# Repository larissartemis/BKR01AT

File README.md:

# BKR01AT
Reavaliação de Circuitos Impressos - BKR01AT - IC / UFAL

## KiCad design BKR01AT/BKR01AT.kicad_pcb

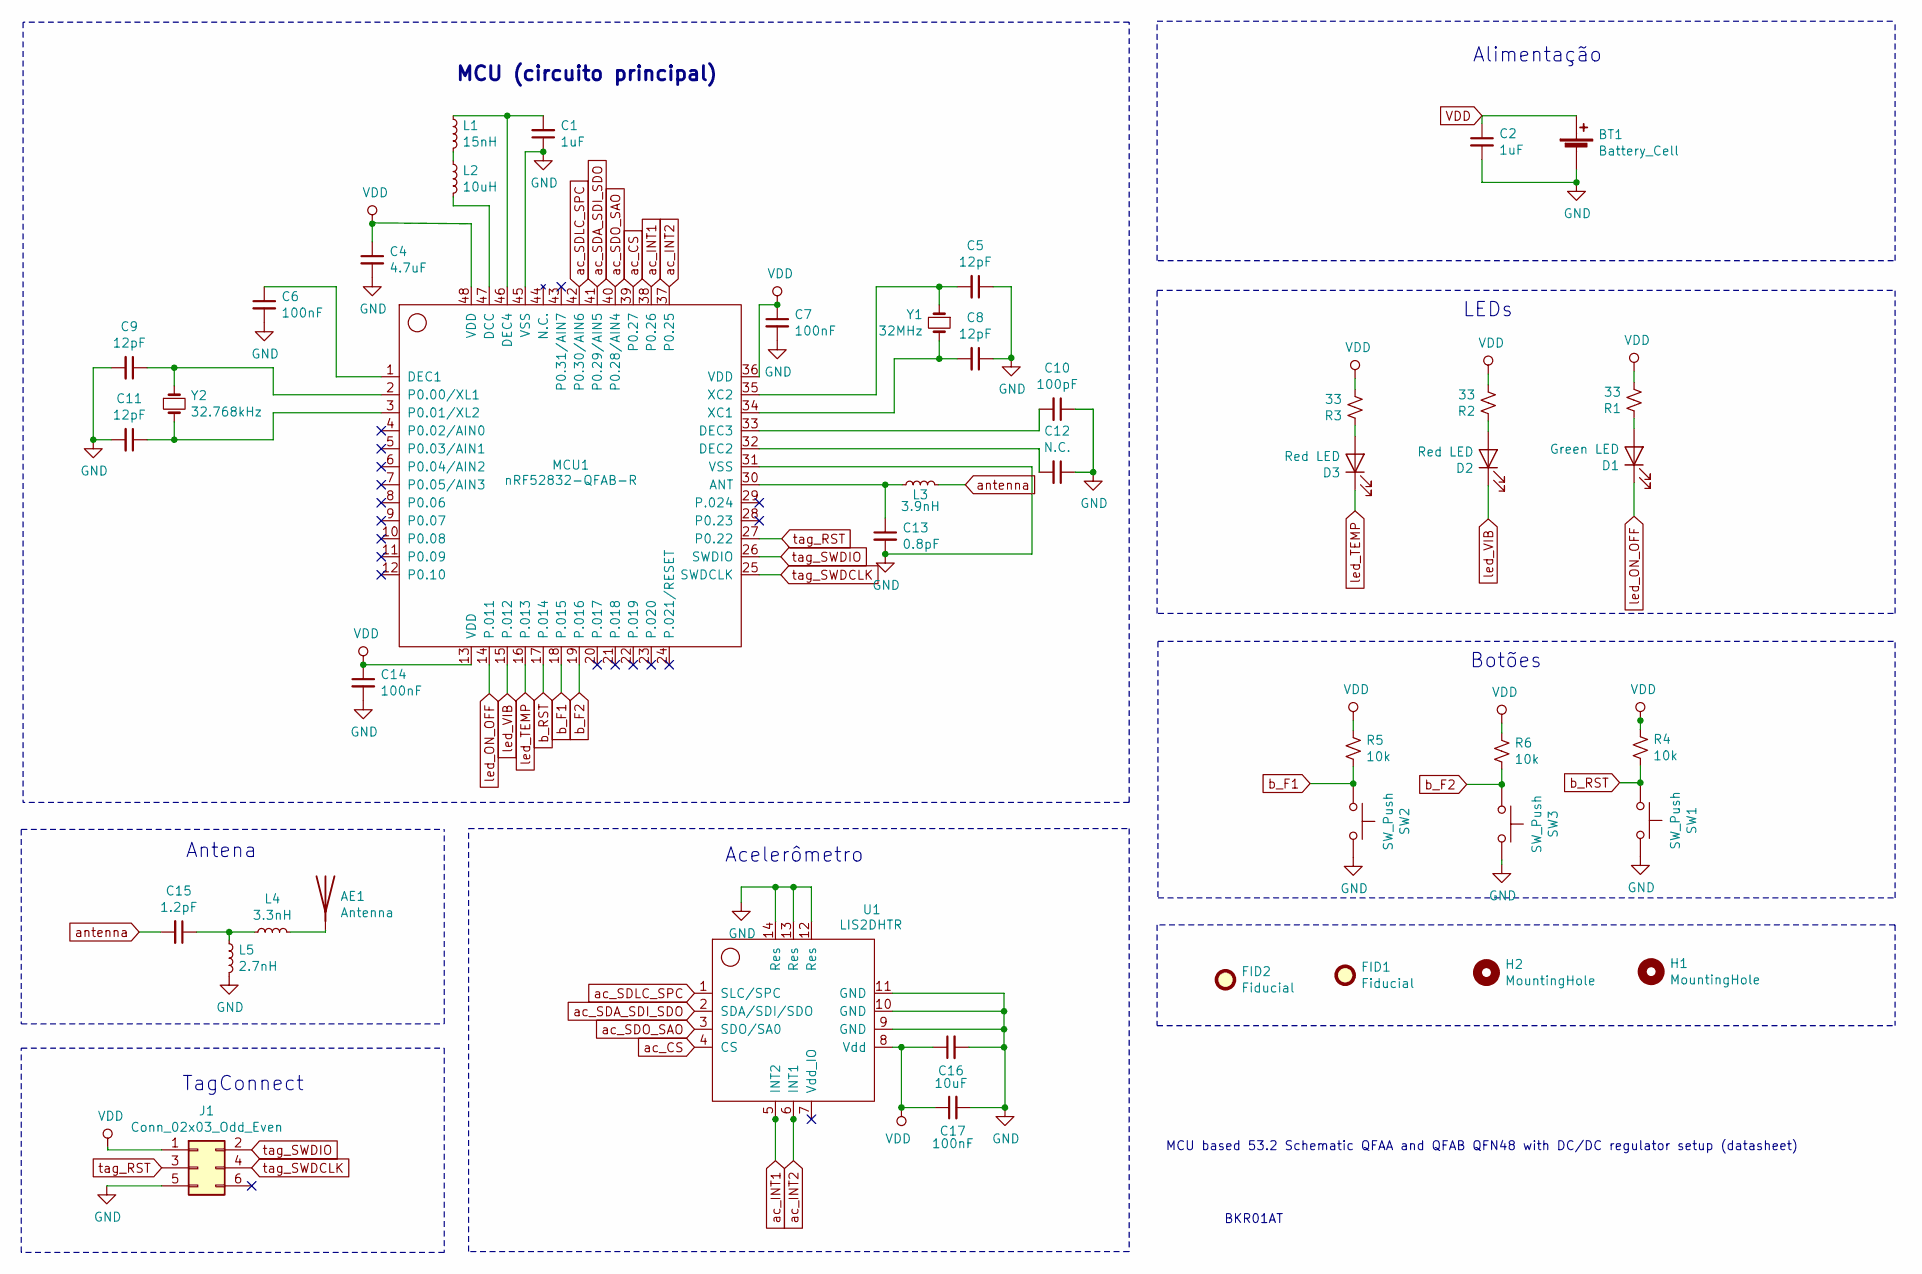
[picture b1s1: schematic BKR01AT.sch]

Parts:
AE1: Antenna; ANT_2450AT18B100E; Part Number 2450AT18B100E
BT1: Battery_Cell; BatteryHolder_MPD_BC2003_1x2032; Part Number CR2032R-HE1
C1, C2: 1uF; C_0402_1005Metric
C4: 4.7uF; C_0402_1005Metric
C5, C8, C9, C11: 12pF; C_0402_1005Metric
C6, C7, C14, C17: 100nF; C_0402_1005Metric
C10: 100pF; C_0402_1005Metric
C12: N.C.; C_0402_1005Metric
C13: 0.8pF; C_0402_1005Metric
C15: 1.2pF; C_0402_1005Metric
C16: 10uF; C_0402_1005Metric
D1: Green LED; LED_0603_1608Metric; Part Number 150060VS75000
D2: Red LED; LED_0603_1608Metric; Part Number 150060VS75000
D3: Red LED; LED_0603_1608Metric; Part Number 150060RS75000
FID1, FID2: Fiducial; Fiducial_0.5mm_Mask1mm
H1, H2: MountingHole; MountingHole_3.2mm_M3
J1: Conn_02x03_Odd_Even; Tag-Connect_TC2030-IDC-NL_2x03_P1.27mm_Vertical
L1: 15nH; L_0402_1005Metric
L2: 10uH; L_0402_1005Metric
L3: 3.9nH; L_0402_1005Metric
L4: 3.3nH; L_0402_1005Metric
L5: 2.7nH; L_0402_1005Metric
MCU1: nRF52832-QFAB-R; QFN-48-1EP_6x6mm_P0.4mm_EP4.6x4.6mm; Part Number nRF52832-QFAB-R
R1, R2, R3: 33; R_0402_1005Metric
R4, R5, R6: 10k; R_0402_1005Metric
SW1, SW2, SW3: SW_Push; SW_PUSH_6mm_H4.3mm; Part Number PTS636 SL43 LFS
U1: LIS2DHTR; LGA-14_2x2mm_P0.35mm_LayoutBorder3x4y; Part Number LIS2DHTR
Y1: 32MHz; Crystal_SMD_2016-4Pin_2.0x1.6mm
Y2: 32.768kHz; Crystal_SMD_3215-2Pin_3.2x1.5mm

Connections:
GND: BT1.2 (-), C1.1, C2.2, C4.2, C5.1, C6.2, C7.2, C8.1, C9.2, C10.1, C11.2, C12.1, C13.2, C14.2, C16.2, C17.2, J1.5, L5.2, MCU1.31 (VSS), MCU1.45 (VSS), SW1.2, SW2.2, SW3.2, U1.9 (GND), U1.10 (GND), U1.11 (GND), U1.12 (Res), U1.13 (Res), U1.14 (Res)
unnamed: AE1.1, L4.2
unnamed: C1.2, L1.1, MCU1.46 (DEC4)
unnamed: C5.2, MCU1.35 (XC2), Y1.1
unnamed: C6.1, MCU1.1 (DEC1)
unnamed: C8.2, MCU1.34 (XC1), Y1.2
unnamed: C9.1, MCU1.2 (P0.00/XL1), Y2.1
unnamed: C10.2, MCU1.33 (DEC3)
unnamed: C11.1, MCU1.3 (P0.01/XL2), Y2.2
unnamed: C12.2, MCU1.32 (DEC2)
unnamed: C13.1, L3.1, MCU1.30 (ANT)
unnamed: C15.1, L4.1, L5.1
unnamed: D1.2 (A), R1.1
unnamed: D2.2 (A), R2.1
unnamed: D3.2 (A), R3.1
unnamed: L1.2, L2.1
unnamed: L2.2, MCU1.47 (DCC)
VDD: BT1.1 (+), C2.1, C4.1, C7.1, C14.1, C16.1, C17.1, J1.1, MCU1.13 (VDD), MCU1.36 (VDD), MCU1.48 (VDD), R1.2, R2.2, R3.2, R4.1, R5.1, R6.1, U1.8 (Vdd)
ac_CS: MCU1.39 (P0.27), U1.4 (CS)
ac_INT1: MCU1.38 (P0.26), U1.5 (INT2)
ac_INT2: MCU1.37 (P0.25), U1.6 (INT1)
ac_SDA_SDI_SDO: MCU1.41 (P0.29/AIN5), U1.2 (SDA/SDI/SDO)
ac_SDLC_SPC: MCU1.42 (P0.30/AIN6), U1.1 (SLC/SPC)
ac_SDO_SAO: MCU1.40 (P0.28/AIN4), U1.3 (SDO/SA0)
antenna: C15.2, L3.2
b_F1: MCU1.18 (P.015), R5.2, SW2.1
b_F2: MCU1.19 (P.016), R6.2, SW3.1
b_RST: MCU1.17 (P.014), R4.2, SW1.1
led_ON_OFF: D1.1 (K), MCU1.14 (P.011)
led_TEMP: D3.1 (K), MCU1.16 (P.013)
led_VIB: D2.1 (K), MCU1.15 (P.012)
tag_RST: J1.3, MCU1.27 (P0.22)
tag_SWDCLK: J1.4, MCU1.25 (SWDCLK)
tag_SWDIO: J1.2, MCU1.26 (SWDIO)

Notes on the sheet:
MCU based 53.2 Schematic QFAA and QFAB QFN48 with DC/DC regulator setup (datasheet)
BKR01AT
TagConnect
Acelerômetro
Antena
Botões
LEDs
Alimentação
MCU (circuito principal)

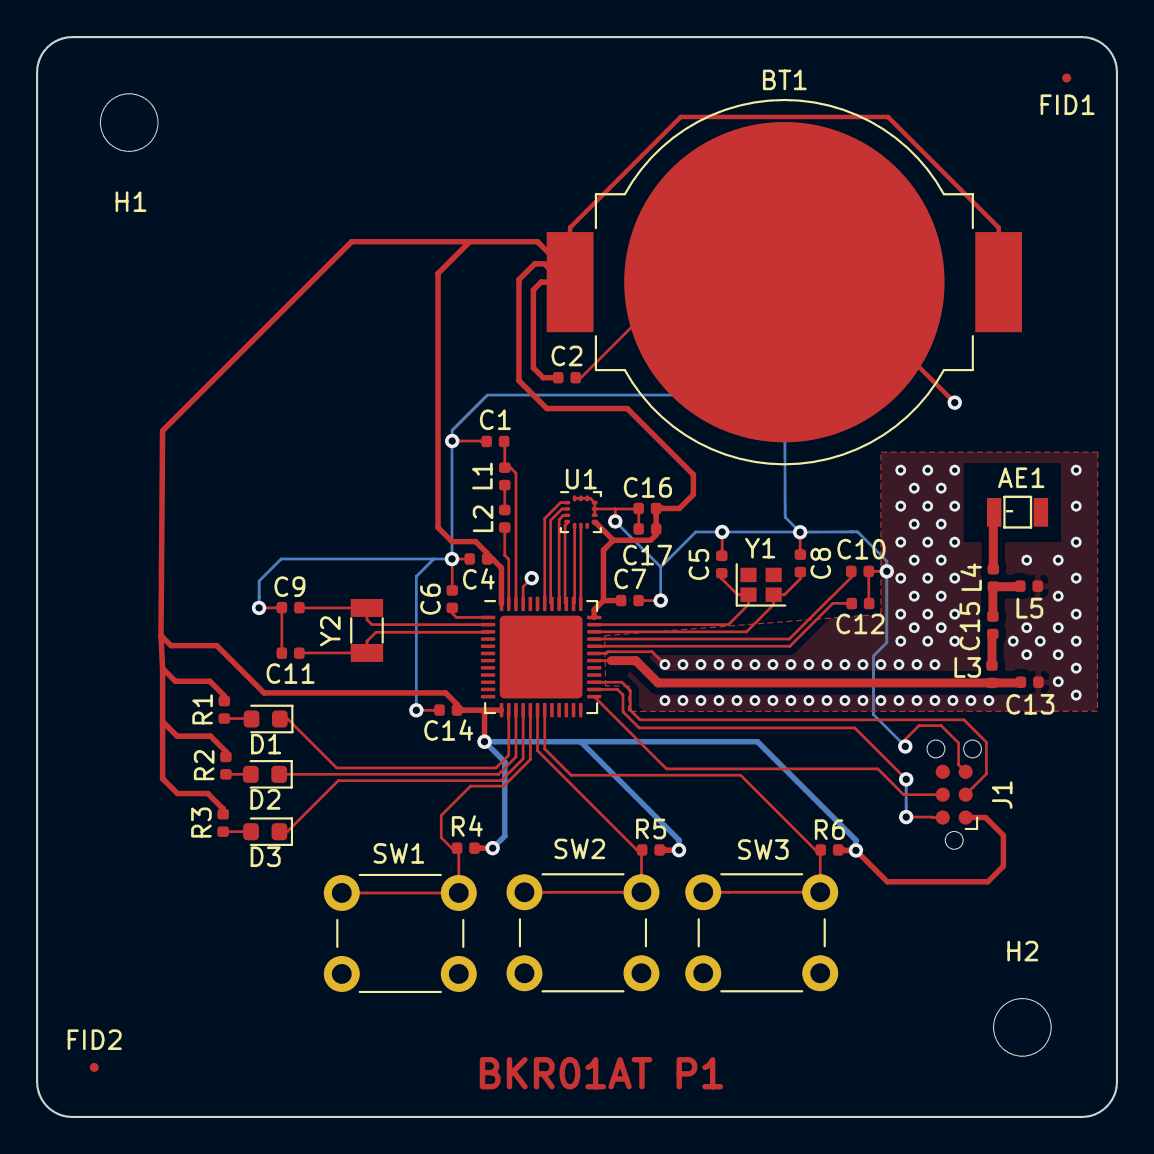
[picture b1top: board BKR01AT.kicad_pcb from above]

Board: 2 copper layers, 60.0 x 60.0 mm, 44 parts (0 on the bottom side), 34 nets.

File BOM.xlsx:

N° | Reference | Quantity |  | Value | Footprint | Datasheet | Part Number | Digikey Part number
 |  | 1 | 1000
1 | AE1 | 1 | 1000 | Antenna | 2450AT18B100E:ANT_2450AT18B100E |  | 2450AT18B100E | 712-1006-2-ND
2 | BT1; BT2 | 2 | 2000 | Battery_Cell | Battery:BatteryHolder_MPD_BC2003_1x2032 |  | CR2032 | 490-18646-ND
3 | C1; C2; C3 | 3 | 3000 | 1uF | Capacitor_SMD:C_0402_1005Metric |  | GRM0335C1E1R0CA01J | 490-7749-1-ND
4 | C4 | 1 | 1000 | 4.7uF | Capacitor_SMD:C_0402_1005Metric |  | GRM0335C1E4R7CA01J | 490-11299-1-ND
5 | C5; C8; C9; C11 | 4 | 4000 | 12pF | Capacitor_SMD:C_0402_1005Metric |  | GRM0335C1E120JA01J | 490-3144-1-ND
6 | C6; C7; C14; C17 | 4 | 4000 | 100nF | Capacitor_SMD:C_0402_1005Metric |  | Not Fitted CAP | Not Fitted CAP
7 | C10 | 1 | 1000 | 100pF | Capacitor_SMD:C_0402_1005Metric |  | GRM0335C1E101JA01J | 490-3160-1-ND
8 | C12 | 1 | 1000 | N.C. | Capacitor_SMD:C_0402_1005Metric |  | Not Fitted CAP | Not Fitted CAP
9 | C13 | 1 | 1000 | 0.8pF | Capacitor_SMD:C_0402_1005Metric |  | GRM0335C1ER80BA01D | 490-6111-1-ND
10 | C15 | 1 | 1000 | 1.2pF | Capacitor_SMD:C_0402_1005Metric |  | GRM0335C1H1R2CA01D | 490-6119-1-ND
11 | C16 | 1 | 1000 | 10uF | Capacitor_SMD:C_0402_1005Metric |  | GRM155R60J106ME05D | 490-GRM155R60J106ME05DCT-ND
12 | D1 | 1 | 1000 | Green LED | LED_SMD:LED_0603_1608Metric |  | 150060VS75000 | 732-4980-2-ND
13 | D2; D3 | 2 | 2000 | Red LED | LED_SMD:LED_0603_1608Metric |  | 150060RS75000 | 732-4978-2-ND
14 | FID1; FID2 | 2 | 2000 | Fiducial | Fiducial:Fiducial_0.5mm_Mask1mm |  | Not Fitted | Not Fitted
15 | H1; H2 | 2 | 2000 | MountingHole | MountingHole:MountingHole_3.2mm_M3 |  | Not Fitted | Not Fitted
16 | J1 | 1 | 1000 | Conn_02x03_Odd_Even | Connector:Tag-Connect_TC2030-IDC-NL_2x03_P1.27mm_Vertical |  | Not Fitted | Not Fitted
17 | L1 | 1 | 1000 | 15nH | Inductor_SMD:L_0402_1005Metric |  | HK100515NJ-T | 587-1521-1-ND
18 | L2 | 1 | 1000 | 10uH | Inductor_SMD:L_0402_1005Metric |  | CV201210-100K | CV201210-100KTR-ND
19 | L3 | 1 | 1000 | 3.9nH | Inductor_SMD:L_0402_1005Metric |  | L-07C3N9SV6T | 712-1459-1-ND
20 | L4 | 1 | 1000 | 3.3nH | Inductor_SMD:L_0402_1005Metric |  | HKQ0603U3N3B-T | 587-4600-1-ND
21 | L5 | 1 | 1000 | 2.7nH | Inductor_SMD:L_0402_1005Metric |  | HK10052N7S-T | 587-1505-2-ND
22 | MCU1 | 1 | 1000 | nRF52832-QFAB-R | Package_DFN_QFN:QFN-48-1EP_6x6mm_P0.4mm_EP4.6x4.6mm |  | NRF52832-QFAB-R | 1490-1055-2-ND
23 | R1; R2; R3 | 3 | 3000 | 33 | Resistor_SMD:R_0402_1005Metric |  | PFR05S-330-JNH | 2037-PFR05S-330-JNHTR-ND
24 | R4; R5; R6 | 3 | 3000 | 10k | Resistor_SMD:R_0402_1005Metric |  | RC0402FR-0710KL | 311-10.0KLRCT-ND
25 | SW1; SW2; SW3 | 3 | 3000 | SW_Push | Button_Switch_THT:SW_PUSH_6mm_H4.3mm |  | PTS636 SL43 SMTR LFS | CKN12309-2-ND
26 | U1 | 1 | 1000 | LIS2DHTR | Package_LGA:LGA-14_2x2mm_P0.35mm_LayoutBorder3x4y |  | LIS2DHTR | 497-13795-2-ND
27 | Y1 | 1 | 1000 | 32MHz | Crystal:Crystal_SMD_2016-4Pin_2.0x1.6mm |  | CX2016DB32000D0WZRC1 | 1253-1586-2-ND
28 | Y2 | 1 | 1000 | 32.768kHz | Crystal:Crystal_SMD_3215-2Pin_3.2x1.5mm |  | CM7V-T1A-32.768KHZ-9PF-20PPM-TA-QC | 2195-CM7V-T1A-32.768KHZ-9PF-20PPM-TA-QCTR-ND

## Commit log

2020-02-26 requisitos
    adicionado um arquivo listando os requisitos do projeto
2020-02-26 BOM
    adicionado arquivo-base para o BOM
2020-02-26 datasheets
    adicionados os datasheets dos equipamentos usados neste projeto
2020-02-26 KiCad
    adicionado o projeto do KiCad
2020-02-26 organizando o esquemático
2020-02-27 LEDs
    ajustadadas as resistências pros LEDs e pros botões
2020-02-27 BOM
    correções no BOM
2020-02-27 Resistores
    resistências ajustadas, considerando agora a tensão do led
    r = (v_bateria - v_led) / i_led
2020-02-27 WIP: PCB
2020-02-28 PCB: trilhas
2020-02-28 PCB
    clearence
2020-02-29 PCB
    trilhas de alimentação, shielding e stitching da antena
2020-02-29 arquivo com os requisitos atualizado
2020-02-29 Update BOM.xlsx
    BOM pra DigiKey
2020-02-29 Carrinho na Digikey
2020-02-29 gerbers
2020-02-29 corrigido o logo da empresa
